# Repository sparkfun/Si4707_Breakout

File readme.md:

SparkFun Si4707 Weather Band Radio Receiver
==================================

[*SparkFun Si4707 Weather Band Radio Breakout (WRL-11129)*](https://www.sparkfun.com/products/11129)

The Si4707 IC is the industry's first weather band (WB) radio receiver to include a specific area message encoding (SAME) processor. 

Features:

* Weather band support (162.4–162.55 MHz)
* SAME processor
* 1050 Hz alert tone detection
* Frequency synthesizer with integrated VCO
* WB digital tuning
* Programmable reference clock
* 2.7 to 5.5 V supply voltage

Repository Contents
-------------------
* **/Firmware** - Arduino example sketch
* **/Hardware** - PCB design files (created with version 6.2.0 of Eagle)
* **/Production** - Production panel files (.brd)
* [Wiki](https://github.com/sparkfun/Si4707_Breakout/wiki) - Be sure to check out the [hardware support](https://github.com/sparkfun/Si4707_Breakout/wiki/Si4707-Breakout-Hardware-Support) page for more information on using the Si4707 breakout board.

Documentation
--------------
* **[Hookup Guide](https://learn.sparkfun.com/tutorials/si4707-hookup-guide)** - Basic hookup guide for the sI4707.
* **[SparkFun Fritzing repo](https://github.com/sparkfun/Fritzing_Parts)** - Fritzing diagrams for SparkFun products.
* **[SparkFun 3D Model repo](https://github.com/sparkfun/3D_Models)** - 3D models of SparkFun products. 

License Information
-------------------
This product is _**open source**_! 

The **hardware** is released under [Creative Commons ShareAlike 4.0 International](https://creativecommons.org/licenses/by-sa/4.0/).

The **code** is beerware; if you see me (or any other SparkFun employee) at the local, and you've found our code helpful, please buy us a round!

Please use, reuse, and modify these files as you see fit. Please maintain attribution to SparkFun Electronics and release anything derivative under the same license.

Distributed as-is; no warranty is given.

- Your friends at SparkFun.

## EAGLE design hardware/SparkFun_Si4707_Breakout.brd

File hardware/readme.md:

# What Are these Files?

The .sch and .brd files hare are Eagle CAD schematic and PCB design files.

These files were created with Eagle 6.2.0, you'll need Eagle 6.0 or later to open them up. There is a free, lite, version of Eagle available from [cadsoftusa.com](cadsoftusa.com).

# Board Features

# License

This product is open source! These Eagle files are released under the Creative Commons Share-Alike Attribution license ([CC BY-SA 3.0](http://creativecommons.org/licenses/by-sa/3.0/us/)).

Please use, reuse, and modify these files as you see fit. Please maintain attribution and release anything derivative under the same license.

- Your friends at SparkFun.

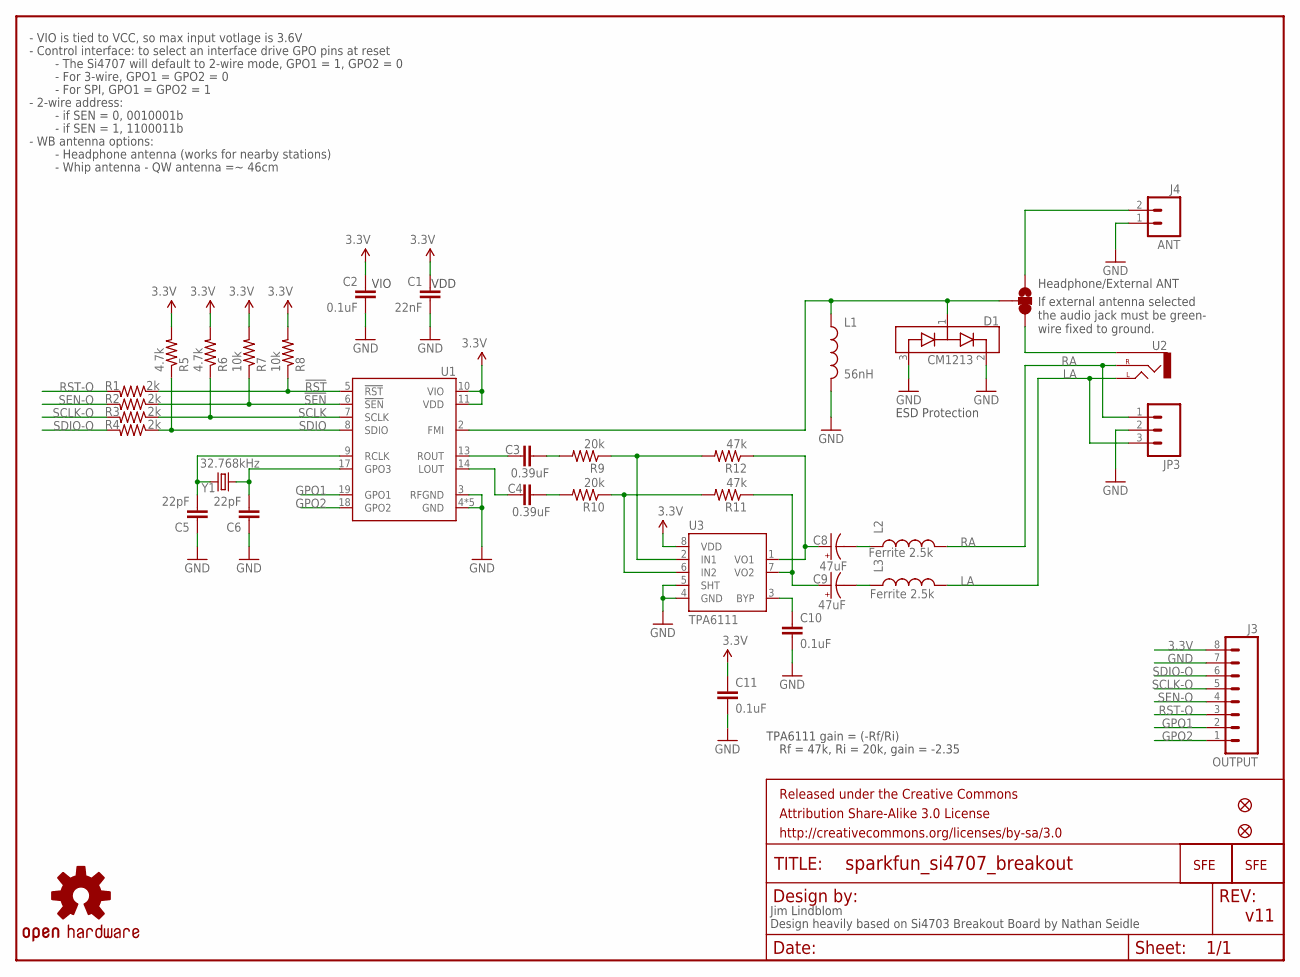
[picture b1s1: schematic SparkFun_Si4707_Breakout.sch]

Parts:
C1: 22nF; 0402-CAP
C2, C10, C11: 0.1uF; 0402-CAP
C3, C4: 0.39uF; 0402-CAP
C5, C6: 22pF; 0402-CAP
C8, C9: 47uF; EIA3528
D1: CM1213; SOT23-3
FRAME1: FRAME-LETTER; CREATIVE_COMMONS
J3: OUTPUT; 1X08
J4: ANT; 1X02
JP1: LOGO-SFENEW; SFE-NEW-WEBLOGO
JP2: LOGO-SFESK; SFE-LOGO-FLAME
JP3: M03PTH; 1X03
JP4, JP5: FIDUCIALUFIDUCIAL; MICRO-FIDUCIAL
L1: 56nH; 0603
L2, L3: Ferrite 2.5k; C0402
R1, R2, R3, R4: 2k; 0402-RES
R5, R6: 4.7k; 0402-RES
R7, R8: 10k; 0402-RES
R9, R10: 20k; 0402-RES
R11, R12: 47k; 0402-RES
SJ2: SOLDERJUMPER_2WAYS; SJ_3
U1: SI4707; SI470X
U2: AUDIO-JACKSMD2; AUDIO-JACK-3.5MM-SMD
U3: TPA6111; SPARKFUN_SO08
U$2: OSHW-LOGOS; OSHW-LOGO-S
Y1: 32.768kHz; CRYSTAL-32KHZ-SMD

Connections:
3.3V: C1.1, C2.1, C11.1, J3.8, R5.2, R6.2, R7.2, R8.2, U1.10 (VIO), U1.11 (VDD), U3.8 (VDD)
!RST: R1.1, R8.1, U1.5 (!RST)
!SEN: R2.1, R7.1, U1.6 (!SEN)
GND: C1.2, C2.2, C5.1, C6.1, C10.2, C11.2, D1.2 (VP), D1.3 (VN), J3.7, J4.1, JP3.2, L1.2, U1.3 (RFGND), U1.4 (GND), U1.12 (GND), U1.15 (GND), U1.16 (GND), U1.21 (GND), U3.4 (GND), U3.5 (SHT)
GPO1: J3.2, U1.19 (GPO1)
GPO2: J3.1, U1.18 (GPO2)
J1: D1.1 (CH1), L1.1, SJ2.2, U1.2 (FMI)
LA: JP3.3, L3.2, U2.TIP (LEFT)
LOUT: C4.1, U1.14 (LOUT)
unnamed: C3.2, R9.2
unnamed: C4.2, R10.2
unnamed: C6.2, U1.17 (GPO3), Y1.X1 (1)
unnamed: SJ2.1, U2.SLEEVE
unnamed: J4.2, SJ2.3
unnamed: R9.1, R12.2, U3.2 (IN1)
unnamed: R10.1, R11.2, U3.6 (IN2)
unnamed: C10.1, U3.3 (BYP)
unnamed: C8.C (-), L2.1
unnamed: C9.C (-), L3.1
unnamed: C8.A (+), R12.1, U3.1 (VO1)
unnamed: C9.A (+), R11.1, U3.7 (VO2)
RA: JP3.1, L2.2, U2.RING (RIGHT)
RCLK: C5.2, U1.9 (RCLK), Y1.X2 (2)
ROUT: C3.1, U1.13 (ROUT)
RST-O: J3.3, R1.2
SCLK: R3.1, R6.1, U1.7 (SCLK)
SCLK-O: J3.5, R3.2
SDIO: R4.1, R5.1, U1.8 (SDIO)
SDIO-O: J3.6, R4.2
SEN-O: J3.4, R2.2

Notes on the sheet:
Jim Lindblom
VDD
VIO
Design heavily based on Si4703 Breakout Board by Nathan Seidle
- VIO is tied to VCC, so max input votlage is 3.6V
- Control interface: to select an interface drive GPO pins at reset
- The Si4707 will default to 2-wire mode, GPO1 = 1, GPO2 = 0
- For 3-wire, GPO1 = GPO2 = 0
- For SPI, GPO1 = GPO2 = 1
- 2-wire address:
- if SEN = 0, 0010001b
- if SEN = 1, 1100011b
- WB antenna options:
- Headphone antenna (works for nearby stations)
- Whip antenna - QW antenna =~ 46cm
ESD Protection
Headphone/External ANT
TPA6111 gain = (-Rf/Ri)
Rf = 47k, Ri = 20k, gain = -2.35
If external antenna selected the audio jack must be green- wire fixed to ground.
v11

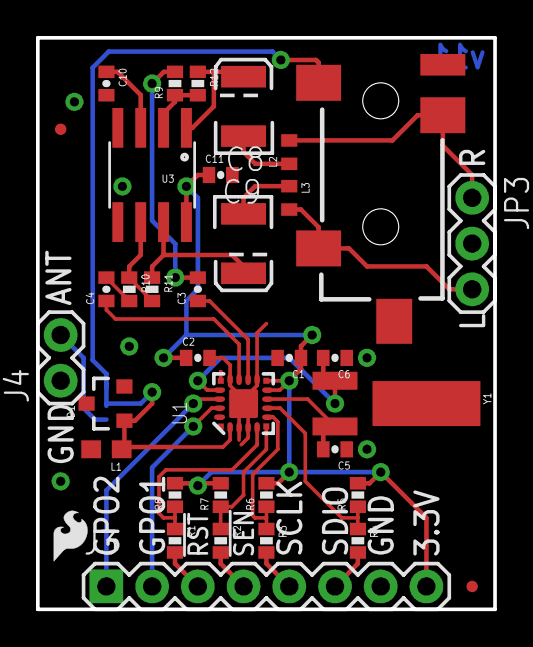
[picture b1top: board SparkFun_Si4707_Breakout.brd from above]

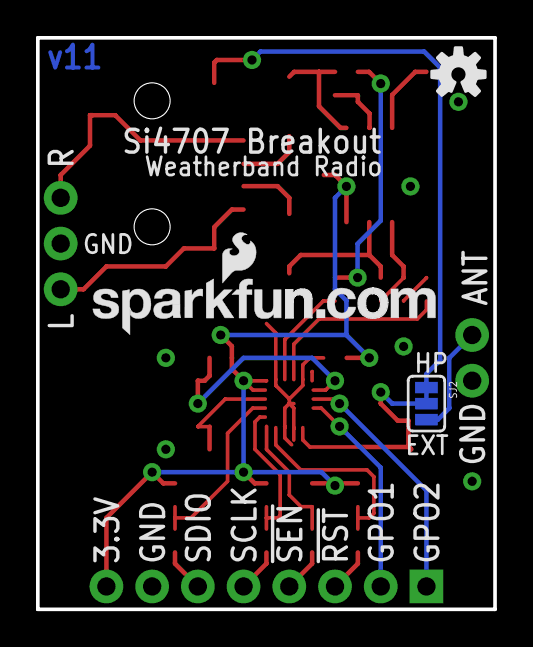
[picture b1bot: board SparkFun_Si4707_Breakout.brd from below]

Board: 2 copper layers, 25.4 x 31.8 mm, 40 parts (3 on the bottom side), 30 nets.

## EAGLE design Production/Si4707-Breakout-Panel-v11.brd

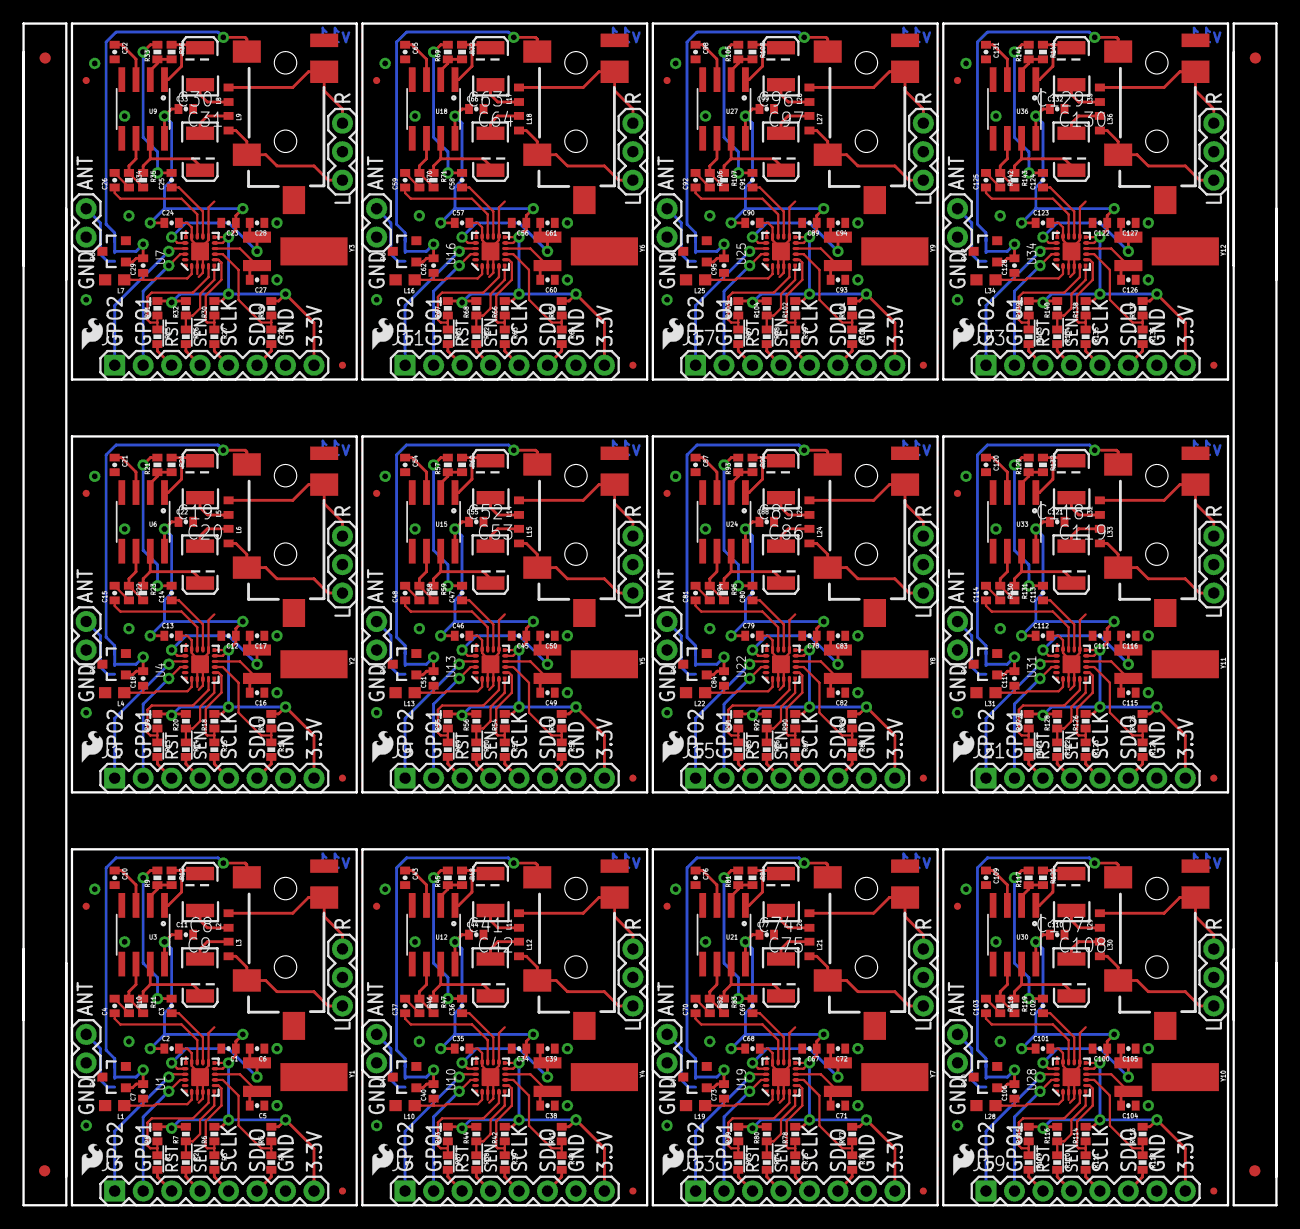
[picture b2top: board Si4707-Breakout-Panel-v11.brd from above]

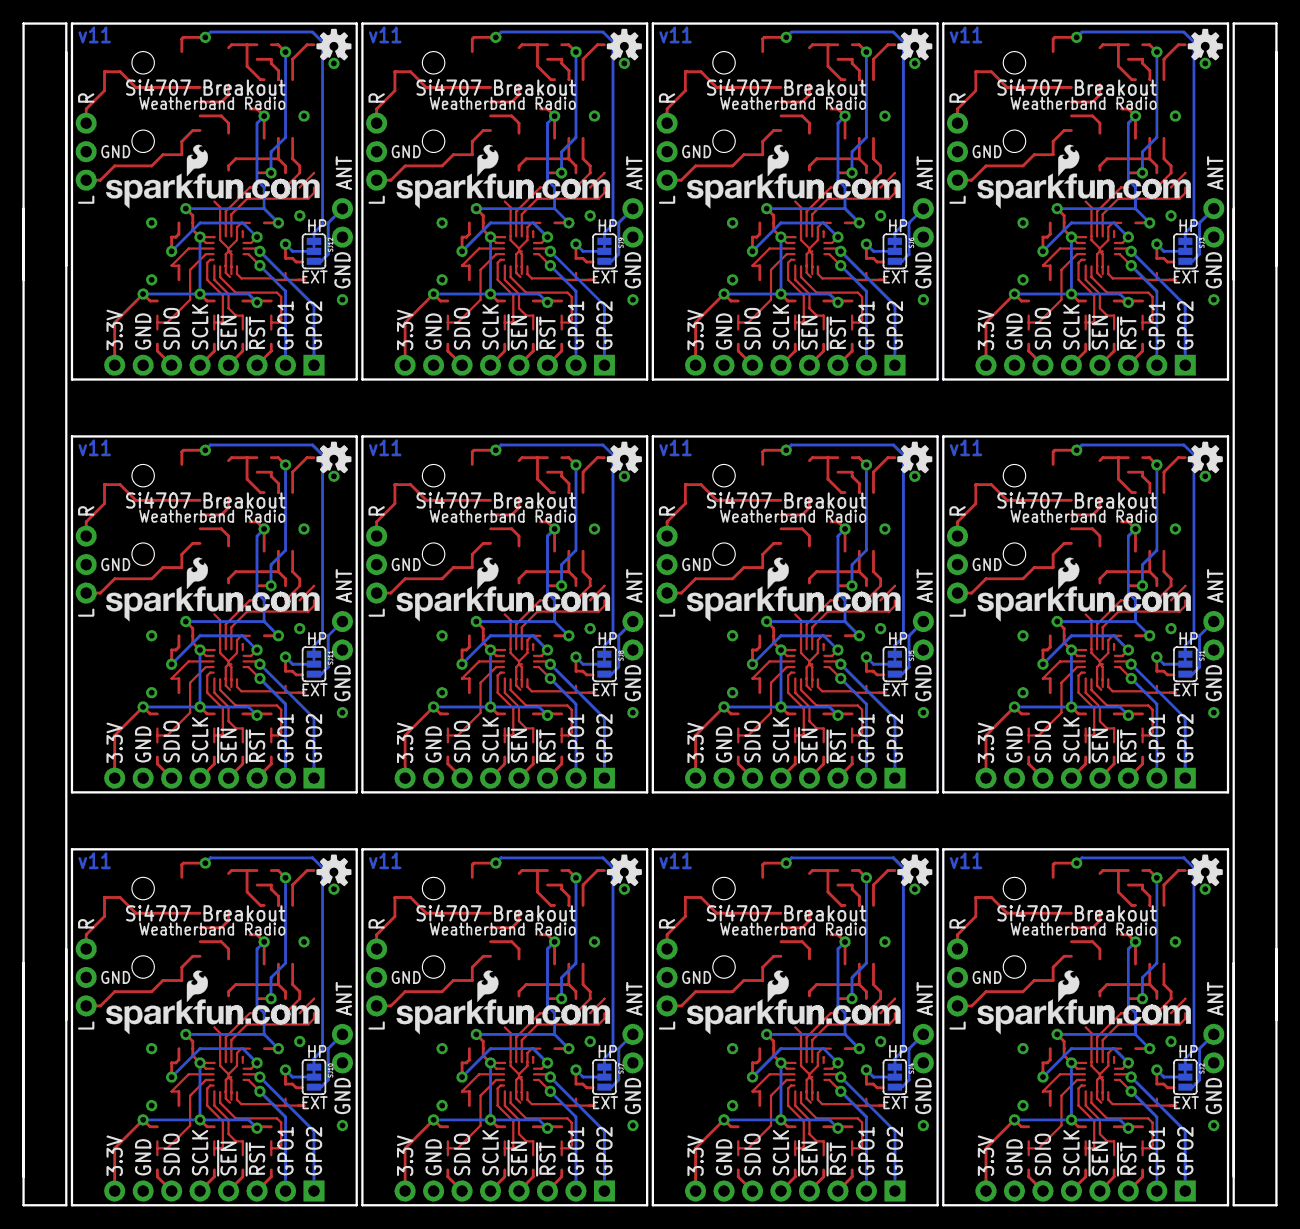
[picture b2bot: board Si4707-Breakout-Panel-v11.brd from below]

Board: 2 copper layers, 111.8 x 105.4 mm, 484 parts (36 on the bottom side), 372 nets.

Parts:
C1, C12, C23, C34, C45, C56, C67, C78, C89, C100, C111, C122: 22nF; 0402-CAP
C2, C10, C11, C13, C21, C22, C24, C32, C33, C35, C43, C44, C46, C54, C55, C57, C65, C66, C68, C76, C77, C79, C87, C88, C90, C98, C99, C101, C109, C110, C112, C120, C121, C123, C131, C132: 0.1uF; 0402-CAP
C3, C4, C14, C15, C25, C26, C36, C37, C47, C48, C58, C59, C69, C70, C80, C81, C91, C92, C102, C103, C113, C114, C124, C125: 0.39uF; 0402-CAP
C5, C6, C16, C17, C27, C28, C38, C39, C49, C50, C60, C61, C71, C72, C82, C83, C93, C94, C104, C105, C115, C116, C126, C127: 22pF; 0402-CAP
C7, C18, C29, C40, C51, C62, C73, C84, C95, C106, C117, C128: 1nF; 0402-CAP
C8, C9, C19, C20, C30, C31, C41, C42, C52, C53, C63, C64, C74, C75, C85, C86, C96, C97, C107, C108, C118, C119, C129, C130: 47uF; EIA3528
D1, D2, D3, D4, D5, D6, D7, D8, D9, D10, D11, D12: CM1213; SOT23-3
E$1, E$2, E$3, E$4: FIDUCIAL-1X2
J1, J3, J5, J7, J9, J11, J13, J15, J17, J19, J21, J23: OUTPUT; 1X08
J2, J4, J6, J8, J10, J12, J14, J16, J18, J20, J22, J24: ANT; 1X02
JP1, JP6, JP11, JP16, JP21, JP26, JP31, JP36, JP41, JP46, JP51, JP56: LOGO-SFENEW; SFE-NEW-WEBLOGO
JP2, JP7, JP12, JP17, JP22, JP27, JP32, JP37, JP42, JP47, JP52, JP57: LOGO-SFESK; SFE-LOGO-FLAME
JP3, JP8, JP13, JP18, JP23, JP28, JP33, JP38, JP43, JP48, JP53, JP58: 1X03
JP4, JP5, JP9, JP10, JP14, JP15, JP19, JP20, JP24, JP25, JP29, JP30, JP34, JP35, JP39, JP40, JP44, JP45, JP49, JP50, JP54, JP55, JP59, JP60: FIDUCIALUFIDUCIAL; MICRO-FIDUCIAL
L1, L4, L7, L10, L13, L16, L19, L22, L25, L28, L31, L34: 56nH; 0603
L2, L3, L5, L6, L8, L9, L11, L12, L14, L15, L17, L18, L20, L21, L23, L24, L26, L27, L29, L30, L32, L33, L35, L36: Ferrite 2.5k; C0402
R1, R2, R3, R4, R13, R14, R15, R16, R25, R26, R27, R28, R37, R38, R39, R40, R49, R50, R51, R52, R61, R62, R63, R64, R73, R74, R75, R76, R85, R86, R87, R88, R97, R98, R99, R100, R109, R110, R111, R112, R121, R122, R123, R124, R133, R134, R135, R136: 2k; 0402-RES
R5, R6, R17, R18, R29, R30, R41, R42, R53, R54, R65, R66, R77, R78, R89, R90, R101, R102, R113, R114, R125, R126, R137, R138: 4.7k; 0402-RES
R7, R8, R19, R20, R31, R32, R43, R44, R55, R56, R67, R68, R79, R80, R91, R92, R103, R104, R115, R116, R127, R128, R139, R140: 10k; 0402-RES
R9, R10, R21, R22, R33, R34, R45, R46, R57, R58, R69, R70, R81, R82, R93, R94, R105, R106, R117, R118, R129, R130, R141, R142: 20k; 0402-RES
R11, R12, R23, R24, R35, R36, R47, R48, R59, R60, R71, R72, R83, R84, R95, R96, R107, R108, R119, R120, R131, R132, R143, R144: 47k; 0402-RES
SJ1, SJ2, SJ3, SJ4, SJ5, SJ6, SJ7, SJ8, SJ9, SJ10, SJ11, SJ12: SJ_3
U1, U4, U7, U10, U13, U16, U19, U22, U25, U28, U31, U34: SI470X
U2, U5, U8, U11, U14, U17, U20, U23, U26, U29, U32, U35: AUDIO-JACK-3.5MM-SMD
U3, U6, U9, U12, U15, U18, U21, U24, U27, U30, U33, U36: TPA6111; SPARKFUN_SO08
U$1, U$2, U$3, U$4, U$5, U$6, U$7, U$8, U$9, U$10, U$11, U$12: OSHW-LOGOS; OSHW-LOGO-S
Y1, Y2, Y3, Y4, Y5, Y6, Y7, Y8, Y9, Y10, Y11, Y12: 32.768kHz; CRYSTAL-32KHZ-SMD

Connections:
3.3V: C1.1, C2.1, C11.1, J3.8, R5.2, R6.2, R7.2, R8.2, U1.10, U1.11, U3.8
3.3V1: C12.1, C13.1, C22.1, J1.8, R17.2, R18.2, R19.2, R20.2, U4.10, U4.11, U6.8
3.3V2: C23.1, C24.1, C33.1, J5.8, R29.2, R30.2, R31.2, R32.2, U7.10, U7.11, U9.8
3.3V3: C34.1, C35.1, C44.1, J7.8, R41.2, R42.2, R43.2, R44.2, U10.10, U10.11, U12.8
3.3V4: C45.1, C46.1, C55.1, J9.8, R53.2, R54.2, R55.2, R56.2, U13.10, U13.11, U15.8
3.3V5: C56.1, C57.1, C66.1, J11.8, R65.2, R66.2, R67.2, R68.2, U16.10, U16.11, U18.8
3.3V6: C67.1, C68.1, C77.1, J13.8, R77.2, R78.2, R79.2, R80.2, U19.10, U19.11, U21.8
3.3V7: C78.1, C79.1, C88.1, J15.8, R89.2, R90.2, R91.2, R92.2, U22.10, U22.11, U24.8
3.3V8: C89.1, C90.1, C99.1, J17.8, R101.2, R102.2, R103.2, R104.2, U25.10, U25.11, U27.8
3.3V9: C100.1, C101.1, C110.1, J19.8, R113.2, R114.2, R115.2, R116.2, U28.10, U28.11, U30.8
3.3V10: C111.1, C112.1, C121.1, J21.8, R125.2, R126.2, R127.2, R128.2, U31.10, U31.11, U33.8
3.3V11: C122.1, C123.1, C132.1, J23.8, R137.2, R138.2, R139.2, R140.2, U34.10, U34.11, U36.8
!RST: R1.1, R8.1, U1.5
!RST1: R13.1, R19.1, U4.5
!RST2: R25.1, R31.1, U7.5
!RST3: R37.1, R43.1, U10.5
!RST4: R49.1, R55.1, U13.5
!RST5: R61.1, R67.1, U16.5
!RST6: R73.1, R79.1, U19.5
!RST7: R85.1, R91.1, U22.5
!RST8: R97.1, R103.1, U25.5
!RST9: R109.1, R115.1, U28.5
!RST10: R121.1, R127.1, U31.5
!RST11: R133.1, R139.1, U34.5
!SEN: R2.1, R7.1, U1.6
!SEN1: R14.1, R20.1, U4.6
!SEN2: R26.1, R32.1, U7.6
!SEN3: R38.1, R44.1, U10.6
!SEN4: R50.1, R56.1, U13.6
!SEN5: R62.1, R68.1, U16.6
!SEN6: R74.1, R80.1, U19.6
!SEN7: R86.1, R92.1, U22.6
!SEN8: R98.1, R104.1, U25.6
!SEN9: R110.1, R116.1, U28.6
!SEN10: R122.1, R128.1, U31.6
!SEN11: R134.1, R140.1, U34.6
GND: C1.2, C2.2, C5.1, C6.1, C10.2, C11.2, D1.2, D1.3, J3.7, J4.1, JP3.2, L1.2, U1.3, U1.4, U1.12, U1.15, U1.16, U1.21, U3.4, U3.5
GND1: C12.2, C13.2, C16.1, C17.1, C21.2, C22.2, D2.2, D2.3, J1.7, J2.1, JP8.2, L4.2, U4.3, U4.4, U4.12, U4.15, U4.16, U4.21, U6.4, U6.5
GND2: C23.2, C24.2, C27.1, C28.1, C32.2, C33.2, D3.2, D3.3, J5.7, J6.1, JP13.2, L7.2, U7.3, U7.4, U7.12, U7.15, U7.16, U7.21, U9.4, U9.5
GND3: C34.2, C35.2, C38.1, C39.1, C43.2, C44.2, D4.2, D4.3, J7.7, J8.1, JP18.2, L10.2, U10.3, U10.4, U10.12, U10.15, U10.16, U10.21, U12.4, U12.5
GND4: C45.2, C46.2, C49.1, C50.1, C54.2, C55.2, D5.2, D5.3, J9.7, J10.1, JP23.2, L13.2, U13.3, U13.4, U13.12, U13.15, U13.16, U13.21, U15.4, U15.5
GND5: C56.2, C57.2, C60.1, C61.1, C65.2, C66.2, D6.2, D6.3, J11.7, J12.1, JP28.2, L16.2, U16.3, U16.4, U16.12, U16.15, U16.16, U16.21, U18.4, U18.5
GND6: C67.2, C68.2, C71.1, C72.1, C76.2, C77.2, D7.2, D7.3, J13.7, J14.1, JP33.2, L19.2, U19.3, U19.4, U19.12, U19.15, U19.16, U19.21, U21.4, U21.5
GND7: C78.2, C79.2, C82.1, C83.1, C87.2, C88.2, D8.2, D8.3, J15.7, J16.1, JP38.2, L22.2, U22.3, U22.4, U22.12, U22.15, U22.16, U22.21, U24.4, U24.5
GND8: C89.2, C90.2, C93.1, C94.1, C98.2, C99.2, D9.2, D9.3, J17.7, J18.1, JP43.2, L25.2, U25.3, U25.4, U25.12, U25.15, U25.16, U25.21, U27.4, U27.5
GND9: C100.2, C101.2, C104.1, C105.1, C109.2, C110.2, D10.2, D10.3, J19.7, J20.1, JP48.2, L28.2, U28.3, U28.4, U28.12, U28.15, U28.16, U28.21, U30.4, U30.5
GND10: C111.2, C112.2, C115.1, C116.1, C120.2, C121.2, D11.2, D11.3, J21.7, J22.1, JP53.2, L31.2, U31.3, U31.4, U31.12, U31.15, U31.16, U31.21, U33.4, U33.5
GND11: C122.2, C123.2, C126.1, C127.1, C131.2, C132.2, D12.2, D12.3, J23.7, J24.1, JP58.2, L34.2, U34.3, U34.4, U34.12, U34.15, U34.16, U34.21, U36.4, U36.5
GPO1: J3.2, U1.19
GPO2: J3.1, U1.18
GPO3: J1.2, U4.19
GPO4: J1.1, U4.18
GPO5: J5.2, U7.19
GPO6: J5.1, U7.18
GPO7: J7.2, U10.19
GPO8: J7.1, U10.18
GPO9: J9.2, U13.19
GPO10: J9.1, U13.18
GPO11: J11.2, U16.19
GPO12: J11.1, U16.18
GPO13: J13.2, U19.19
GPO14: J13.1, U19.18
GPO15: J15.2, U22.19
GPO16: J15.1, U22.18
GPO17: J17.2, U25.19
GPO18: J17.1, U25.18
GPO19: J19.2, U28.19
GPO20: J19.1, U28.18
GPO21: J21.2, U31.19
GPO22: J21.1, U31.18
GPO23: J23.2, U34.19
GPO24: J23.1, U34.18
J1: C7.2, D1.1, SJ2.2
J2: C18.2, D2.1, SJ1.2
J3: C29.2, D3.1, SJ3.2
J4: C40.2, D4.1, SJ4.2
J5: C51.2, D5.1, SJ5.2
J6: C62.2, D6.1, SJ6.2
J7: C73.2, D7.1, SJ7.2
J8: C84.2, D8.1, SJ8.2
J9: C95.2, D9.1, SJ9.2
J10: C106.2, D10.1, SJ10.2
J11: C117.2, D11.1, SJ11.2
J12: C128.2, D12.1, SJ12.2
LA: JP3.3, L3.2, U2.TIP
LA1: JP8.3, L6.2, U5.TIP
LA2: JP13.3, L9.2, U8.TIP
LA3: JP18.3, L12.2, U11.TIP
LA4: JP23.3, L15.2, U14.TIP
LA5: JP28.3, L18.2, U17.TIP
LA6: JP33.3, L21.2, U20.TIP
LA7: JP38.3, L24.2, U23.TIP
LA8: JP43.3, L27.2, U26.TIP
LA9: JP48.3, L30.2, U29.TIP
LA10: JP53.3, L33.2, U32.TIP
LA11: JP58.3, L36.2, U35.TIP
LOUT: C4.1, U1.14
LOUT1: C15.1, U4.14
LOUT2: C26.1, U7.14
LOUT3: C37.1, U10.14
LOUT4: C48.1, U13.14
LOUT5: C59.1, U16.14
LOUT6: C70.1, U19.14
LOUT7: C81.1, U22.14
LOUT8: C92.1, U25.14
LOUT9: C103.1, U28.14
LOUT10: C114.1, U31.14
LOUT11: C125.1, U34.14
unnamed: C14.2, R21.2
unnamed: C3.2, R9.2
unnamed: C4.2, R10.2
unnamed: C15.2, R22.2
unnamed: C6.2, U1.17, Y1.X1
unnamed: SJ2.1, U2.SLEEVE
unnamed: C7.1, L1.1, U1.2
unnamed: J4.2, SJ2.3
unnamed: R9.1, R12.2, U3.2
unnamed: R10.1, R11.2, U3.6
unnamed: C10.1, U3.3
unnamed: C8.C, L2.1
unnamed: C9.C, L3.1
unnamed: C8.A, R12.1, U3.1
unnamed: C9.A, R11.1, U3.7
unnamed: C17.2, U4.17, Y2.X1
unnamed: C18.1, L4.1, U4.2
unnamed: SJ1.1, U5.SLEEVE
unnamed: J2.2, SJ1.3
unnamed: R21.1, R24.2, U6.2
unnamed: R22.1, R23.2, U6.6
unnamed: C21.1, U6.3
unnamed: C19.C, L5.1
unnamed: C20.C, L6.1
unnamed: C19.A, R24.1, U6.1
unnamed: C20.A, R23.1, U6.7
unnamed: C25.2, R33.2
unnamed: C26.2, R34.2
unnamed: C28.2, U7.17, Y3.X1
unnamed: C29.1, L7.1, U7.2
unnamed: SJ3.1, U8.SLEEVE
unnamed: J6.2, SJ3.3
unnamed: R33.1, R36.2, U9.2
unnamed: R34.1, R35.2, U9.6
unnamed: C32.1, U9.3
unnamed: C30.C, L8.1
unnamed: C31.C, L9.1
unnamed: C30.A, R36.1, U9.1
unnamed: C31.A, R35.1, U9.7
unnamed: C36.2, R45.2
unnamed: C37.2, R46.2
unnamed: C39.2, U10.17, Y4.X1
unnamed: C40.1, L10.1, U10.2
unnamed: SJ4.1, U11.SLEEVE
unnamed: J8.2, SJ4.3
unnamed: R45.1, R48.2, U12.2
unnamed: R46.1, R47.2, U12.6
unnamed: C43.1, U12.3
unnamed: C41.C, L11.1
unnamed: C42.C, L12.1
unnamed: C41.A, R48.1, U12.1
unnamed: C42.A, R47.1, U12.7
unnamed: C47.2, R57.2
unnamed: C48.2, R58.2
unnamed: C50.2, U13.17, Y5.X1
unnamed: C51.1, L13.1, U13.2
unnamed: SJ5.1, U14.SLEEVE
unnamed: J10.2, SJ5.3
unnamed: R57.1, R60.2, U15.2
unnamed: R58.1, R59.2, U15.6
unnamed: C54.1, U15.3
unnamed: C52.C, L14.1
unnamed: C53.C, L15.1
unnamed: C52.A, R60.1, U15.1
unnamed: C53.A, R59.1, U15.7
unnamed: C58.2, R69.2
unnamed: C59.2, R70.2
unnamed: C61.2, U16.17, Y6.X1
unnamed: C62.1, L16.1, U16.2
unnamed: SJ6.1, U17.SLEEVE
unnamed: J12.2, SJ6.3
unnamed: R69.1, R72.2, U18.2
unnamed: R70.1, R71.2, U18.6
unnamed: C65.1, U18.3
unnamed: C63.C, L17.1
unnamed: C64.C, L18.1
unnamed: C63.A, R72.1, U18.1
unnamed: C64.A, R71.1, U18.7
unnamed: C69.2, R81.2
unnamed: C70.2, R82.2
unnamed: C72.2, U19.17, Y7.X1
unnamed: C73.1, L19.1, U19.2
unnamed: SJ7.1, U20.SLEEVE
unnamed: J14.2, SJ7.3
unnamed: R81.1, R84.2, U21.2
unnamed: R82.1, R83.2, U21.6
unnamed: C76.1, U21.3
unnamed: C74.C, L20.1
unnamed: C75.C, L21.1
unnamed: C74.A, R84.1, U21.1
unnamed: C75.A, R83.1, U21.7
unnamed: C80.2, R93.2
unnamed: C81.2, R94.2
unnamed: C83.2, U22.17, Y8.X1
unnamed: C84.1, L22.1, U22.2
unnamed: SJ8.1, U23.SLEEVE
unnamed: J16.2, SJ8.3
unnamed: R93.1, R96.2, U24.2
unnamed: R94.1, R95.2, U24.6
unnamed: C87.1, U24.3
unnamed: C85.C, L23.1
unnamed: C86.C, L24.1
unnamed: C85.A, R96.1, U24.1
unnamed: C86.A, R95.1, U24.7
unnamed: C91.2, R105.2
unnamed: C92.2, R106.2
unnamed: C94.2, U25.17, Y9.X1
unnamed: C95.1, L25.1, U25.2
unnamed: SJ9.1, U26.SLEEVE
unnamed: J18.2, SJ9.3
unnamed: R105.1, R108.2, U27.2
unnamed: R106.1, R107.2, U27.6
unnamed: C98.1, U27.3
unnamed: C96.C, L26.1
unnamed: C97.C, L27.1
unnamed: C96.A, R108.1, U27.1
unnamed: C97.A, R107.1, U27.7
unnamed: C102.2, R117.2
unnamed: C103.2, R118.2
unnamed: C105.2, U28.17, Y10.X1
unnamed: C106.1, L28.1, U28.2
unnamed: SJ10.1, U29.SLEEVE
unnamed: J20.2, SJ10.3
unnamed: R117.1, R120.2, U30.2
unnamed: R118.1, R119.2, U30.6
unnamed: C109.1, U30.3
unnamed: C107.C, L29.1
unnamed: C108.C, L30.1
unnamed: C107.A, R120.1, U30.1
unnamed: C108.A, R119.1, U30.7
unnamed: C113.2, R129.2
unnamed: C114.2, R130.2
unnamed: C116.2, U31.17, Y11.X1
unnamed: C117.1, L31.1, U31.2
unnamed: SJ11.1, U32.SLEEVE
unnamed: J22.2, SJ11.3
unnamed: R129.1, R132.2, U33.2
unnamed: R130.1, R131.2, U33.6
unnamed: C120.1, U33.3
unnamed: C118.C, L32.1
unnamed: C119.C, L33.1
unnamed: C118.A, R132.1, U33.1
unnamed: C119.A, R131.1, U33.7
unnamed: C124.2, R141.2
unnamed: C125.2, R142.2
unnamed: C127.2, U34.17, Y12.X1
unnamed: C128.1, L34.1, U34.2
unnamed: SJ12.1, U35.SLEEVE
unnamed: J24.2, SJ12.3
unnamed: R141.1, R144.2, U36.2
unnamed: R142.1, R143.2, U36.6
unnamed: C131.1, U36.3
unnamed: C129.C, L35.1
unnamed: C130.C, L36.1
unnamed: C129.A, R144.1, U36.1
unnamed: C130.A, R143.1, U36.7
RA: JP3.1, L2.2, U2.RING
RA1: JP8.1, L5.2, U5.RING
RA2: JP13.1, L8.2, U8.RING
RA3: JP18.1, L11.2, U11.RING
RA4: JP23.1, L14.2, U14.RING
RA5: JP28.1, L17.2, U17.RING
RA6: JP33.1, L20.2, U20.RING
RA7: JP38.1, L23.2, U23.RING
RA8: JP43.1, L26.2, U26.RING
RA9: JP48.1, L29.2, U29.RING
RA10: JP53.1, L32.2, U32.RING
RA11: JP58.1, L35.2, U35.RING
RCLK: C5.2, U1.9, Y1.X2
RCLK1: C16.2, U4.9, Y2.X2
RCLK2: C27.2, U7.9, Y3.X2
RCLK3: C38.2, U10.9, Y4.X2
RCLK4: C49.2, U13.9, Y5.X2
RCLK5: C60.2, U16.9, Y6.X2
RCLK6: C71.2, U19.9, Y7.X2
RCLK7: C82.2, U22.9, Y8.X2
RCLK8: C93.2, U25.9, Y9.X2
RCLK9: C104.2, U28.9, Y10.X2
RCLK10: C115.2, U31.9, Y11.X2
RCLK11: C126.2, U34.9, Y12.X2
ROUT: C3.1, U1.13
ROUT1: C14.1, U4.13
ROUT2: C25.1, U7.13
ROUT3: C36.1, U10.13
ROUT4: C47.1, U13.13
ROUT5: C58.1, U16.13
ROUT6: C69.1, U19.13
ROUT7: C80.1, U22.13
ROUT8: C91.1, U25.13
ROUT9: C102.1, U28.13
ROUT10: C113.1, U31.13
ROUT11: C124.1, U34.13
RST-O: J3.3, R1.2
RST-O1: J1.3, R13.2
RST-O2: J5.3, R25.2
RST-O3: J7.3, R37.2
RST-O4: J9.3, R49.2
RST-O5: J11.3, R61.2
RST-O6: J13.3, R73.2
RST-O7: J15.3, R85.2
RST-O8: J17.3, R97.2
RST-O9: J19.3, R109.2
RST-O10: J21.3, R121.2
RST-O11: J23.3, R133.2
SCLK: R3.1, R6.1, U1.7
SCLK1: R15.1, R18.1, U4.7
SCLK2: R27.1, R30.1, U7.7
SCLK3: R39.1, R42.1, U10.7
SCLK4: R51.1, R54.1, U13.7
SCLK5: R63.1, R66.1, U16.7
SCLK6: R75.1, R78.1, U19.7
SCLK7: R87.1, R90.1, U22.7
SCLK8: R99.1, R102.1, U25.7
SCLK9: R111.1, R114.1, U28.7
SCLK10: R123.1, R126.1, U31.7
SCLK11: R135.1, R138.1, U34.7
SCLK-O: J3.5, R3.2
SCLK-O1: J1.5, R15.2
SCLK-O2: J5.5, R27.2
SCLK-O3: J7.5, R39.2
SCLK-O4: J9.5, R51.2
SCLK-O5: J11.5, R63.2
SCLK-O6: J13.5, R75.2
SCLK-O7: J15.5, R87.2
SCLK-O8: J17.5, R99.2
SCLK-O9: J19.5, R111.2
SCLK-O10: J21.5, R123.2
SCLK-O11: J23.5, R135.2
SDIO: R4.1, R5.1, U1.8
SDIO1: R16.1, R17.1, U4.8
SDIO2: R28.1, R29.1, U7.8
SDIO3: R40.1, R41.1, U10.8
SDIO4: R52.1, R53.1, U13.8
SDIO5: R64.1, R65.1, U16.8
SDIO6: R76.1, R77.1, U19.8
SDIO7: R88.1, R89.1, U22.8
SDIO8: R100.1, R101.1, U25.8
SDIO9: R112.1, R113.1, U28.8
SDIO10: R124.1, R125.1, U31.8
SDIO11: R136.1, R137.1, U34.8
SDIO-O: J3.6, R4.2
SDIO-O1: J1.6, R16.2
SDIO-O2: J5.6, R28.2
SDIO-O3: J7.6, R40.2
SDIO-O4: J9.6, R52.2
SDIO-O5: J11.6, R64.2
SDIO-O6: J13.6, R76.2
SDIO-O7: J15.6, R88.2
SDIO-O8: J17.6, R100.2
SDIO-O9: J19.6, R112.2
SDIO-O10: J21.6, R124.2
SDIO-O11: J23.6, R136.2
SEN-O: J3.4, R2.2
SEN-O1: J1.4, R14.2
SEN-O2: J5.4, R26.2
SEN-O3: J7.4, R38.2
SEN-O4: J9.4, R50.2
SEN-O5: J11.4, R62.2
SEN-O6: J13.4, R74.2
SEN-O7: J15.4, R86.2
SEN-O8: J17.4, R98.2
SEN-O9: J19.4, R110.2
SEN-O10: J21.4, R122.2
SEN-O11: J23.4, R134.2

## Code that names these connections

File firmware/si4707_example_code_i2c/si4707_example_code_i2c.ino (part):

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      RST   ----------------------   4 (can be any digital pin)

  Any other pins on the Si4707 breakout can be left unconnected.
  The SEN pin is pulled high, which will affect the I2C address.
  The GPO1/2 pins are not used as outputs, and their default
  states set the Si4707 into I2C mode.
  
  For more information on the Si4707, check out the abundance of
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#include "si4707_definitions.h"
#include <Wire.h>

// In 2-wire mode, connecting the SEN pin to the Arduino is optional.
//  If it's not connected, make sure SEN_ADDRESS is defined as 1
//  assuming SEN is pulled high as on the breakout board.
#define SEN_ADDRESS 1
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}

// initSi4707 performs the following functions, in sequence:
//  * Initialize all pins connected to Si4707 (SEN, SCLK, SDIO, and RST)
//  * Starts up the Wire class - used for two-wire communication
//  * Applies a reset signal to the Si4707
//  * Sends the Power Up command to the Si4707
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  pinMode(rstPin, OUTPUT);  // Reset
  digitalWrite(rstPin, LOW);  // Keep the SI4707 in reset
  
  // Set initial pin value: SEN (I2C Address select)
  pinMode(senPin, OUTPUT);  // Serial enable
  if (SEN_ADDRESS) 
    digitalWrite(senPin, HIGH);
  else 
    digitalWrite(senPin, LOW);
  
  // Set initial pin values: SDIO and SCLK (serial data and clock lines)
  // Wire.begin() will take care of this
  Wire.begin();
  delay(1);  // Short delay before we take reset up
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
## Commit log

2013-01-14 Hardware files - v11
    Also adding readme files.
2013-01-14 Adding bStop to solder jumper.
    Much easier to cut jumpers when they're exposed!
2013-01-15 Production readied
    Added fiducials to design. Created production panel.
2013-03-01 Adding working I2C example code
2013-03-04 Few minor comment fixes
2013-03-20 Cleaning up schematic, matching it up to release
2013-03-29 Updating readme - adding picture, links, license
2013-04-02 Adding wiki info to readme
2013-04-11 Update readme.md
    Finished the beerware description.
2015-05-12 Updating directory structure, adding version to hardware files, updating readme
2019-11-05 Update si4707_system_functions.ino
    Removing unnecessary Wire.endTransmission().
2025-06-27 Update readme.md
    Updating links.

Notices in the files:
firmware/si4707_example_code_i2c/si4707_example_code_i2c.ino:
license: Beerware. Please use, re-use, and modify this code without
parts and their libraries:
SparkFun-RF: Licensing: CC v3.0 Share-Alike You are welcome to use this library for commercial purposes.
SparkFun-Aesthetics: Released under the Creative Commons Attribution Share-Alike 3.0 License
